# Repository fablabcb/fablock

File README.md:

# fablock

This is a mechanic to open our window via a telegram bot to get access to the keys to our workshop.

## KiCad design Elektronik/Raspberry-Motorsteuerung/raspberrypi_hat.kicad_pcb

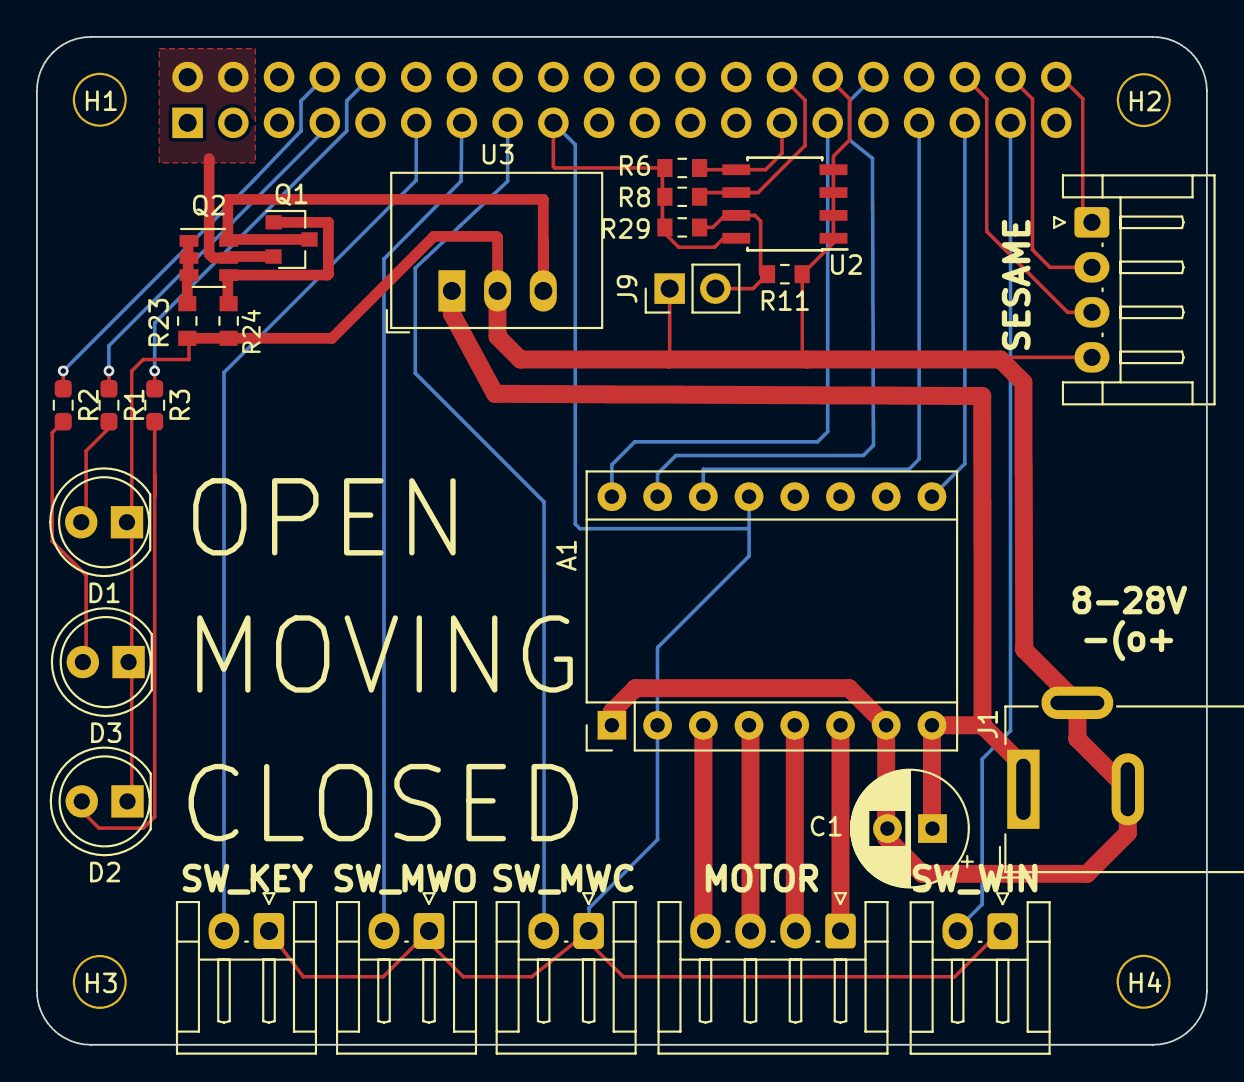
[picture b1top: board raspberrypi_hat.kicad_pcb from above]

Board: 2 copper layers, 65.0 x 56.0 mm, 31 parts (1 on the bottom side), 31 nets.

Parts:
A1: Pololu_Breakout_A4988; Pololu_Breakout-16_15.2x20.3mm
C1: 100UF-63V-20%_ELECT_; CP_Radial_D6.3mm_P2.50mm
D1: LED_RED; LED_D5.0mm
D2: LED_GREEN; LED_D5.0mm
D3: LED_YELLOW; LED_D5.0mm
H1, H2, H3, H4: 3mm_Mounting_Hole; NPTH_3mm_ID
J1: Barrel_Jack_Switch; BarrelJack_Wuerth_6941xx301002
J2, J6: Conn_01x04_Male; JST_EH_S4B-EH_1x04_P2.50mm_Horizontal
J3: 40HAT; PinSocket_2x20_P2.54mm_Vertical
J8, J10, J11, J15: Conn_01x02_Male; JST_EH_S2B-EH_1x02_P2.50mm_Horizontal
J9: CONN_01X02; PinHeader_1x02_P2.54mm_Vertical
Q1: DMG2305UX; SOT-23
Q2: DMMT5401; SOT-23-6
R1: 470; R_0603_1608Metric_Pad0.98x0.95mm_HandSolder
R2: 1K; R_0603_1608Metric_Pad0.98x0.95mm_HandSolder
R3: 680; R_0603_1608Metric_Pad0.98x0.95mm_HandSolder
R6, R8: 3.9K; R_0603_1608Metric_Pad0.84x1.00mm_HandSolder
R11: DNP; R_0603_1608Metric_Pad0.84x1.00mm_HandSolder
R23, R29: 10K; R_0603_1608Metric_Pad0.84x1.00mm_HandSolder
R24: 47K; R_0603_1608Metric_Pad0.84x1.00mm_HandSolder
U2: CAT24C32; SOIC-8_3.9x4.9mm_P1.27mm
U3: R-78E5.0-1.0; Converter_DCDC_RECOM_R-78E-0.5_THT

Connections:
/DRV_DIR: A1.16, J3.29
/DRV_EN: A1.9, J3.35
/DRV_SLP: A1.14, J3.33
/DRV_STP: A1.15, J3.32
/ID_SC_EEPROM: J3.28, R8.2, U2.6
/ID_SD_EEPROM: J3.27, R6.2, U2.5
/IN_KEY: J3.11, J15.2
/IN_MWC: J3.15, J10.2
/IN_MWO: J3.13, J8.2
/IN_WIN: J3.37, J11.2
/LED_CLOSED: J3.10, R3.1
/LED_MOVING: J3.8, R2.1
/LED_OPEN: J3.7, R1.1
/OUT_SESAME_CLOSING: J3.38, J6.2
/OUT_SESAME_OPEN: J3.36, J6.3
/OUT_SESAME_OPENING: J3.40, J6.1
/P3V3: A1.2, A1.13, J3.17, J8.1, J10.1, J11.1, J15.1, R6.1, R8.1, R29.1, U2.8
/P5V: Q1.3, Q2.6, U3.3
/P5V_HAT: J3.2, J3.4, Q1.2, Q2.5
/P12V: A1.8, C1.1, J1.1, U3.1
GND: A1.1, A1.7, C1.2, D1.1, D2.1, D3.1, J1.2, J1.3, J3.30, J6.4, J9.1, R11.2, R23.2, R24.2, U2.1, U2.2, U2.3, U2.4, U3.2
unnamed: A1.3, J2.4
unnamed: A1.4, J2.3
unnamed: A1.5, J2.2
unnamed: A1.6, J2.1
unnamed: D1.2, R1.2
unnamed: D2.2, R3.2
unnamed: D3.2, R2.2
unnamed: J9.2, R11.1, R29.2, U2.7
unnamed: Q1.1, Q2.4, R24.1
unnamed: Q2.1, Q2.2, Q2.3, R23.1

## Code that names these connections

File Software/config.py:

import logging

# set debug level for all modules
logging.basicConfig(
    format="%(asctime)s - %(name)s - %(levelname)s - %(message)s",
    level=logging.INFO,
)
# do not log every polling request
logging.getLogger("httpx").setLevel(logging.WARNING)
# set debug level for states in states.py

NETWORKING_ENABLED = True
NETWORKING_PORT = 55555
TLS_SERVER_CERT_PATH = "/home/pi/server.crt"
TLS_SERVER_KEY_PATH = "/home/pi/server.key"
TLS_CLIENT_CERT_PATH = "/home/pi/client.crt"

OPENING = False
CLOSING = not OPENING

## Pin Numbering Scheme: BCM

# motor driver
DIR = 5  # Direction GPIO Pin
STEP = 12  # Step GPIO Pin
SLEEP = 13  # 0 for sleep
ENABLE = 19  # 0 for enable
# <= 1000 Hz is good for our slim stepper motor
MOTOR_FREQ = 500  # pulses per second
MOTOR_DUTY = 128  # 128 is 50% of 256 (50% off time)

UNLOCKED_TIMEOUT = 12
MOVING_HALTED_TIMEOUT = 12

# LEDs
LED_OPEN = 4
LED_MOVING = 14
LED_CLOSED = 15

# input switches
# push open type (low if pushed, normally closed NC)

# window handle in unlocked position (stop motor if low, if switch is pressed)
SW_LIMIT_OPEN = 27
# window handle in locked position (stop motor if low, if switch is pressed)
SW_LIMIT_CLOSED = 22

# push type (high if pushed, normally open NO)
# window open (stop motor if low, if switch is not pressed)
SW_WINDOW_OPEN = 26

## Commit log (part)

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2017-05-30 Mechanik
2017-05-30 Elektronik: Motorbewegung mit einem Endstopp
2017-05-30 first working version with endstops for Locked, Unlocked and Closed
2017-05-30 Hiermit läuft der Motor jetzt
2018-02-24 Neues Arduino-Board zur Motorsteuerung von Marcel als Submodule integriert
2018-02-24 Roseguarden als submodule hinzugefügt
2018-02-24 Node-Red Telegram Bot that sends notifications whenever someone opens the FabLock
2018-03-01 explain Roseguard and Node-Red configuration
2018-03-03 Erkennt nun ob der Schlüssel geschaltet ist
2018-03-23 delay database read to not disturb roseguard in its write process
2018-03-27 Schlüssel Schalter mit Pullup
2019-10-12 Erste Version Keyring
2020-12-08 Mechanik neu gedruckt
2020-12-22 Raspberry-Motorsteuerung kicad projekt hinzugefügt
2021-01-05 TODO bearbeitet
2021-01-19 finished schema, started pcb
2021-01-26 finished pcb layout
2021-02-09 added gerber files, bom
2021-02-16 improved barrel-jack/capacitor footprint and 12v lanes
2021-02-16 changed to 2 layer board
2021-02-16 changed to 2 layer board (4reals)
2021-02-17 Änderungen zum Keyring Beeper
2021-02-18 increased via size to 0.6/0.3mm
2021-03-18 fixed second SW_KEY to SW_WIN in silkscreen
2021-03-30 fixed LED orientation, C1 symbol, added 'rev 2' label, did not export gerber files
2021-04-20 added begin of raspberry hat software
2021-04-20 fablock_flowchart.drawio
2021-04-27 Software flow diagram initial version
2021-04-27 Software flow diagram: renamed file
2021-04-27 updated TODOs in steppermotor.py
2021-05-18 TODO added
2021-05-18 first draft of python program
2021-06-02 states and transitions implemented
2021-06-02 flow diagram corrected
2021-06-02 added TODOs
2021-06-02 typo in TODO
2021-06-09 Telegram bot integrated
2021-06-09 TODO updated
2021-06-23 secrets in separate file
2021-06-23 CHAT_ID in secrets.py has to be a number
2021-06-23 use logging library, send telegram messages
2021-07-01 systemd file created
2021-07-01 timeouts changed to be devidable by 60
2021-07-01 Added documentation for installation and running in README.md
2023-09-20 small changes for newer python-telegram-bot version 20.x
2023-11-05 deleted old developments
2023-11-05 mechanics: first collection of files and started a README
2023-11-05 .gitignore for kicad files
2023-11-05 moved Elektronik and Sofware folders
2023-11-05 split telegram into receiving and sending
    The telegram receiving can be run in a separate thread to not block
    the main thread, while sending must be easily possible from other
    places in the system.
2023-11-05 fix whitespace
2023-11-05 add start command to find chat id
2023-11-05 update to telegram bot framework 20
2023-11-05 adjust calls to telegram sender
2023-11-05 make telegram display commands
2023-11-05 adjust main loop to new threading model
    Since the telegram command listener is now blocking, it must be run in a separate thread.
    The telegram thread can set an event for the main thread to open the window.
    This also allows for extending by just adding other threads that set the event to open.
2023-11-05 rename functions to snake_case
2023-11-05 update software documentation
2023-11-05 remove unused variables
2023-11-05 improve feedback
    In normal operation, the messages are sent without triggering notifications.
    The message for the opened window is only sent once it is actually open,
    the receipt of the message is only acknowledged by sending a typing marker.
    Normally, a users should be standing in front of the fablock and should thus
    be able to tell that it is operating, independent of feedback on Telegram.
2023-11-12 don't re-export sleep from config
2023-11-12 fix more indentation
2023-11-12 swap telegram into main thread
    The telegram library does some operation involving set_wakeup_fd which
    only works in the main thread.
2023-11-12 dont use threading.Event for signalling
    There seems to be some issue with handling threading.Event in an
    async context. Since setting a global variable works across threads,
    this seems to be the simpler solution.
2023-11-12 check in RFID companion
2023-11-16 fix missing argument
2023-11-25 fixup! fix missing argument
2023-11-25 fix missing return
    If an error occurs while reading, that should not be returned to the
    higher processing layers and be counted as an invalid read.
2023-11-25 fix undefined variable errors; cleanup
2023-11-25 refactor parsing date to separate function
2023-11-25 add telegram command to change expiry date
2023-11-25 move ready LED to different pin
    Using this differnt pin, the cables will be closer together on the
    GPIO pins, making it easier to make an appropriate enclosure for
    the RPi.
2023-12-02 decision to not delay open command
2023-12-02 namespace telegram commands
    To make sure that the commands do not conflict, prefix all commands
    with "rfid_".
2023-12-02 add revoke telegram command
2023-12-02 fix reader timeouts
    The exponential part of the timeouts was previously not correctly
    implemented. This makes it so the timeout will actually be exponential.
2023-12-02 correctly handle error when reading
    Instead of understanding this as an incorrect card, rather handle
    errors while reading as if no card was read.
2023-12-02 add kill switch
2023-12-16 RFID: don't return success if data was read incorrectly
2023-12-16 fixup! add kill switch
2023-12-16 only telegram group admins can run RFID commands
2023-12-16 gitignore pycache
2023-12-16 RFID: different indication when successful
2023-12-16 add logging in telegram setup
2023-12-16 RFID: indicate ready to write
2023-12-16 improve installation docs
2024-01-17 different message when fablock is busy
2024-01-27 add TCP listener
2024-01-27 update configuration
    as found in the running version
2024-01-27 add emoji to telegram messages
2024-01-27 adjust restarting of systemd units
2024-01-27 fix working directory for systemd
2024-01-27 fix a few small bugs
2024-01-27 rfid: use TCP connection
2024-01-27 fix typos
2024-02-04 document TCP server for fablock core
2024-02-12 update fablock installation instructions
    In new Raspbian installations, the use of venv is required for installing
    python packages. Also the directory structure has changed, so linking the
    systemd service file also has to be adjusted.
2024-02-14 tune logging level
2024-02-14 fix telegram API error
    Apparently it does not like single dots when sending as MARKDOWNv2 but
    there is no good documentation on what the meaning of the dot is supposed
    to be.
2024-02-14 fix reconnections
    Previously, the `con` variable was not reset, so it would not
    actually reconnect later.
2024-02-19 add TLS to networking
    Just having TCP and relying on the connection being stable is not
    a good security model. Instead mutual TLS is used to authenticate
    both ends during communication. It also encrypts the traffic which
    is not really necessary, but this also provides authentication.
    Since the certificates might be hard to set up and the networking
    might not be desired, also added a configuration variable to more
2024-02-19 small bugfixes
2024-07-29 fix package name
2024-07-29 save username requesting open
    Users may delete their own message, thus making it impossible to know
    who requested the window to open. By making the bot reply with the username
    it can be saved for posterity, notwithstanding an admin deleting the message.
2024-07-29 simplify installation
2024-07-29 fix: use display name instead of username
    Not all users have a username, but all users have a display name.
    This is a fixup for commit d32e8c04cdc3b882d0561d103a4458bddb39f599.
2025-04-11 mark install script as executable
2025-04-11 retries and better error handling for sending messages
2025-04-11 don't unlock when sending fails
    This keeps the previous behaviour because we do not want the lock to open if it is not logged who did it.
2025-04-11 handle all exceptions
    There can also be other errors like DNS errors.
2025-04-11 ignore outdated messages
    If the fablock crashes and somehow gets restarted when perhaps nobody is present, it should not process old messages.
2025-04-11 properly handle time zone
2025-05-31 fix install order
    Can only create a venv or install python packages if python itself
    is already installed.
2025-05-31 improve install instructions
    - use requirements.txt for python dependencies
    - add install script for RFID-companion
2025-05-31 replace telegram with discourse
2025-06-01 format code
2025-06-01 dont put state enum members in globals
    Using globals can be very confusing because this makes it hard to understand where the values are coming from.
    It also breaks static analysis tools.
2025-06-01 use match/case for state machine
2025-06-01 use threading.Event instead of waiting
    Instead of busy waiting, we can use a threading.Event to wait for an unlock command in the state machine.
2025-06-01 properly encapsulate state machine
    Instead of spreading the state and enter_time variables over multiple files, encapsulate them in a class.
2025-06-12 complete state machine encapsulation
2025-10-03 rename secret config file
    to not conflict with the stdlib module of the same name
2025-10-03 fixup! properly encapsulate state machine
2025-10-03 remove unnecessary use of global variable
2025-10-03 remove unused pin setup
2025-10-03 refactor handlers into OOP
2025-10-03 separate config and hardware handling
2025-10-03 better naming for switches
2025-10-04 rewrite in async
    To fix some issues with the async telegram handler stuff.
2025-10-04 tcp_handler: listen in dual stack
2025-10-04 RFID: improve encapsulation and types
2025-10-04 refactor handlers to allow broadcast requests
    This will allow to "tunnel" messages from handlers through the central
    server in case the handlers have some information to get out.
2025-10-04 RFID: update network protocol
    The network protocol will now transmit the name so it can be transmitted centrally. It also makes use of the new broadcast requests feature.
2025-10-06 remove incorrect limit
    This causes the LimitOverrunError to be raise always because the limit argument in start_server was wrongly assumed to be a limit on connections.
2025-10-06 remove check_socket_alive
    passing flags to SslSocket.recv is not allowed
2025-10-06 fix sqlite3 thread error
2025-10-06 add more logging
2025-10-06 implement retry for sending open command
2025-10-06 RFID: use broadcast instead of telegram
2025-10-06 add discourse handler
2025-10-27 show which handler was used to request open
2026-02-17 discourse: use excerpt instead of message
    This ignores any fancy markup, allowing the use of links that activate the command again.
2026-03-29 remove outdated comment
2026-03-30 add telegram phase out message
